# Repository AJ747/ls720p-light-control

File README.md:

# LS720P Light Control PCB
Controller for LS720P light using ATTINY5. Brightness is controlled using potentiometer. +5V input and switch for power on/off. Made in KiCad 10.

# Schematic

# Images of PCB

Top layer

Bottom layer

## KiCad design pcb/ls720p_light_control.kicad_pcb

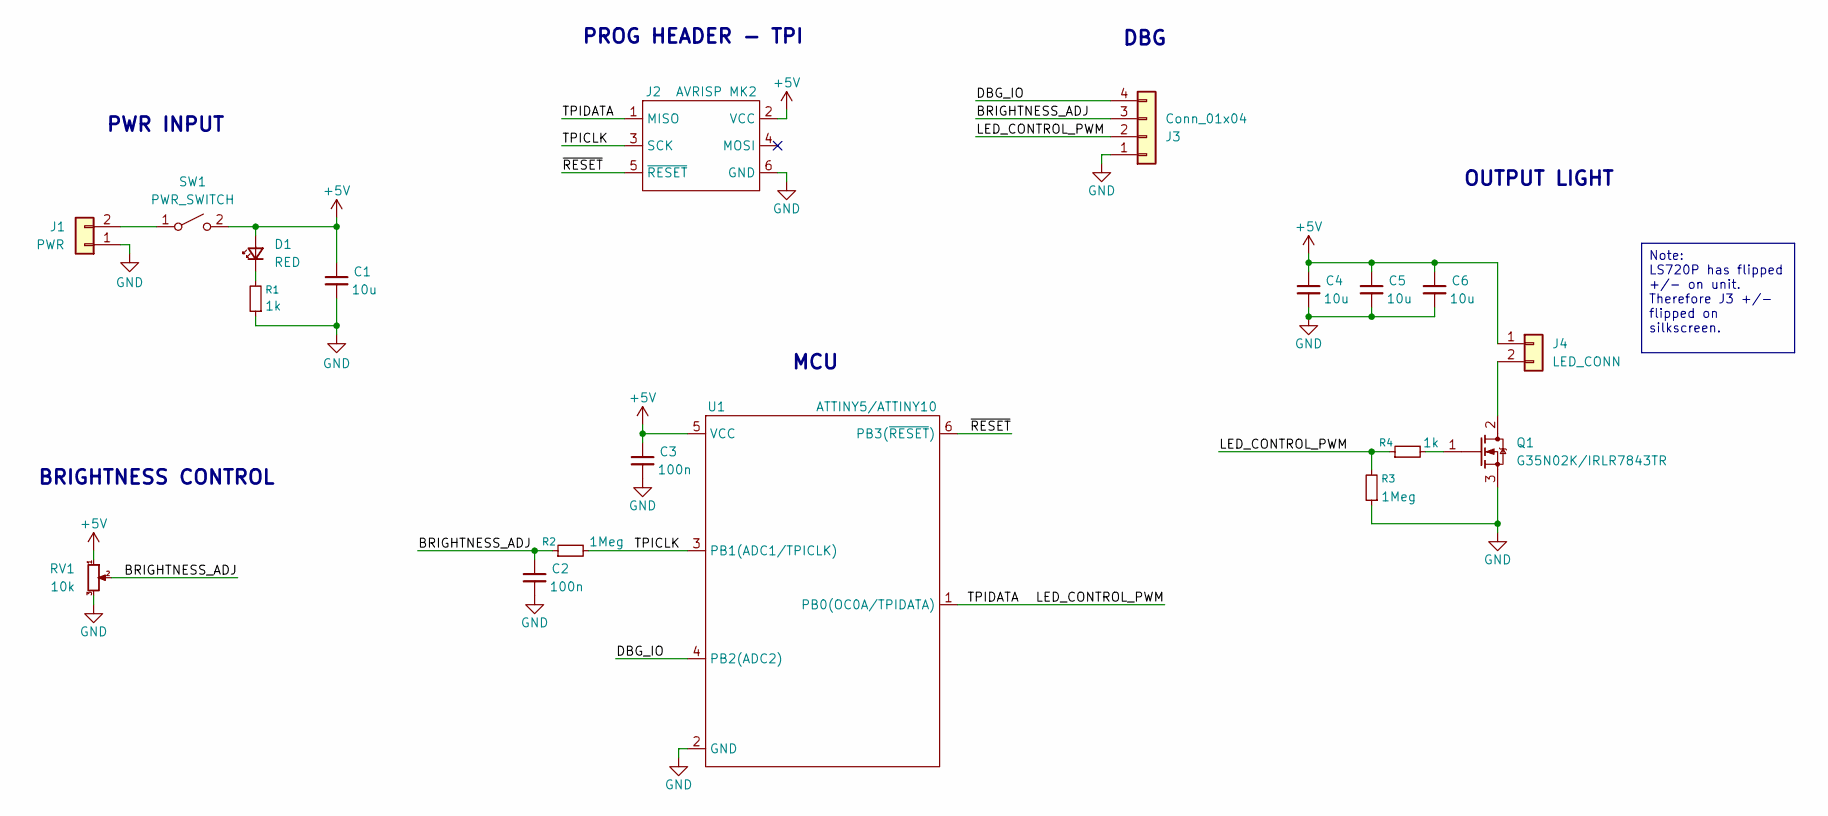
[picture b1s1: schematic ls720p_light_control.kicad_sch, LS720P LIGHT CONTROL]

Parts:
C1, C4, C5, C6: 10u; C_0805_2012Metric_Pad1.18x1.45mm_HandSolder
C2, C3: 100n; C_0603_1608Metric_Pad1.08x0.95mm_HandSolder
D1: RED; LED_0603_1608Metric_Pad1.05x0.95mm_HandSolder
J1: PWR; PinHeader_1x02_P2.54mm_Vertical
J2: AVRISP MK2; PinHeader_2x03_P2.54mm_Vertical
J3: Conn_01x04; PinHeader_1x04_P2.54mm_Vertical
J4: LED_CONN; PinHeader_1x02_P2.54mm_Vertical
Q1: G35N02K/IRLR7843TR; TO-252-2; Part G35N02K
R1, R4: 1k; R_0603_1608Metric_Pad0.98x0.95mm_HandSolder
R2, R3: 1Meg; R_0603_1608Metric_Pad0.98x0.95mm_HandSolder
RV1: 10k; PinHeader_1x03_P2.54mm_Vertical
SW1: PWR_SWITCH; PinHeader_1x02_P2.54mm_Vertical
U1: ATTINY5/ATTINY10; TSOT-23-6_HandSoldering; Part ATTINY5-TSHR

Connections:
+5V: C1.1, C3.1, C4.1, C5.1, C6.1, D1.2 (A), J2.2 (VCC), J4.1, RV1.1, SW1.2 (B), U1.5 (VCC)
/BRIGHTNESS_ADJ: C2.1, J3.3, R2.1, RV1.2
/DBG_IO: J3.4, U1.4 (PB2(ADC2))
/LED_CONTROL_PWM: J2.1 (MISO), J3.2, R3.2, R4.1, U1.1 (PB0(OC0A/TPIDATA))
/TPICLK: J2.3 (SCK), R2.2, U1.3 (PB1(ADC1/TPICLK))
/~RESET: J2.5 (~RESET), U1.6 (PB3(~RESET))
GND: C1.2, C2.2, C3.2, C4.2, C5.2, C6.2, J1.1, J2.6 (GND), J3.1, Q1.3 (S), R1.1, R3.1, RV1.3, U1.2 (GND)
unnamed: D1.1 (K), R1.2
unnamed: J1.2, SW1.1 (A)
unnamed: J4.2, Q1.2 (D)
unnamed: Q1.1 (G), R4.2

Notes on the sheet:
PROG HEADER - TPI
DBG
OUTPUT LIGHT
PWR INPUT
BRIGHTNESS CONTROL
MCU
Note: LS720P has flipped +/- on unit. Therefore J3 +/- flipped on silkscreen.

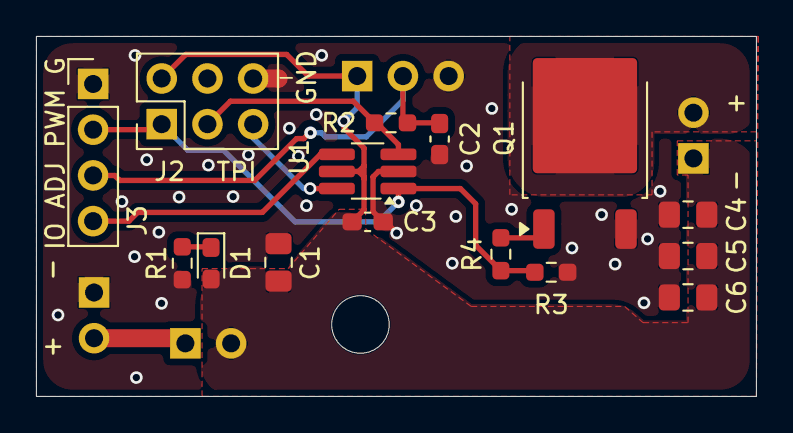
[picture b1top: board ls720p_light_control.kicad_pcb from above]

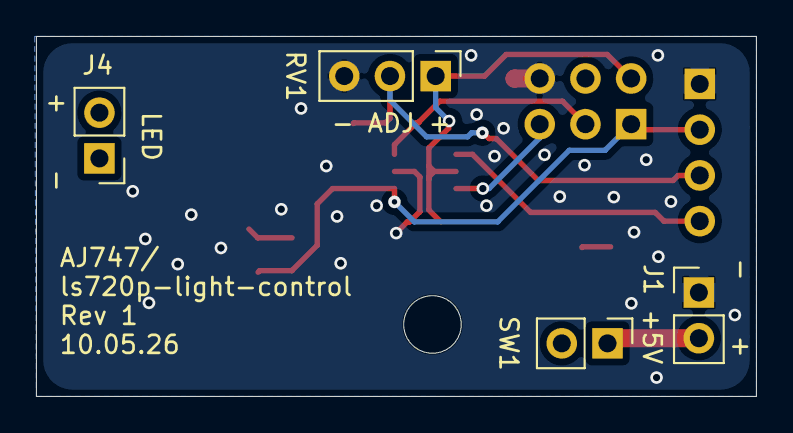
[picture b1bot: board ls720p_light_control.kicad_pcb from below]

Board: 2 copper layers, 40.0 x 20.0 mm, 19 parts (4 on the bottom side), 11 nets.

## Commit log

2026-05-09 Added schematic, pcb layout
2026-05-09 Fix README header formatting and improve description
2026-05-10 added ALT parts for LDO, MOSFET, MCU
2026-05-10 updated mcu info, specified package/part number
2026-05-10 added notes to brightness max comp and output light section
2026-05-10 done placing components
2026-05-10 pcb -> updated placing
2026-05-10 pcb -> finished layout, need to add stitching vias
2026-05-10 pcb -> layout completed
2026-05-10 generated gerber
2026-05-10 docs -> added pictures of pcb
2026-05-10 docs -> alter image
2026-05-10 docs -> added schematic
2026-05-10 Update README with schematic and PCB images
    Added schematic and PCB images to README.
2026-05-10 removed +12v rail, everything is now +5v
    using +12v didn't acheive better brightness when using pwm, so keeping +5v
2026-05-10 updated pictures and pcb
